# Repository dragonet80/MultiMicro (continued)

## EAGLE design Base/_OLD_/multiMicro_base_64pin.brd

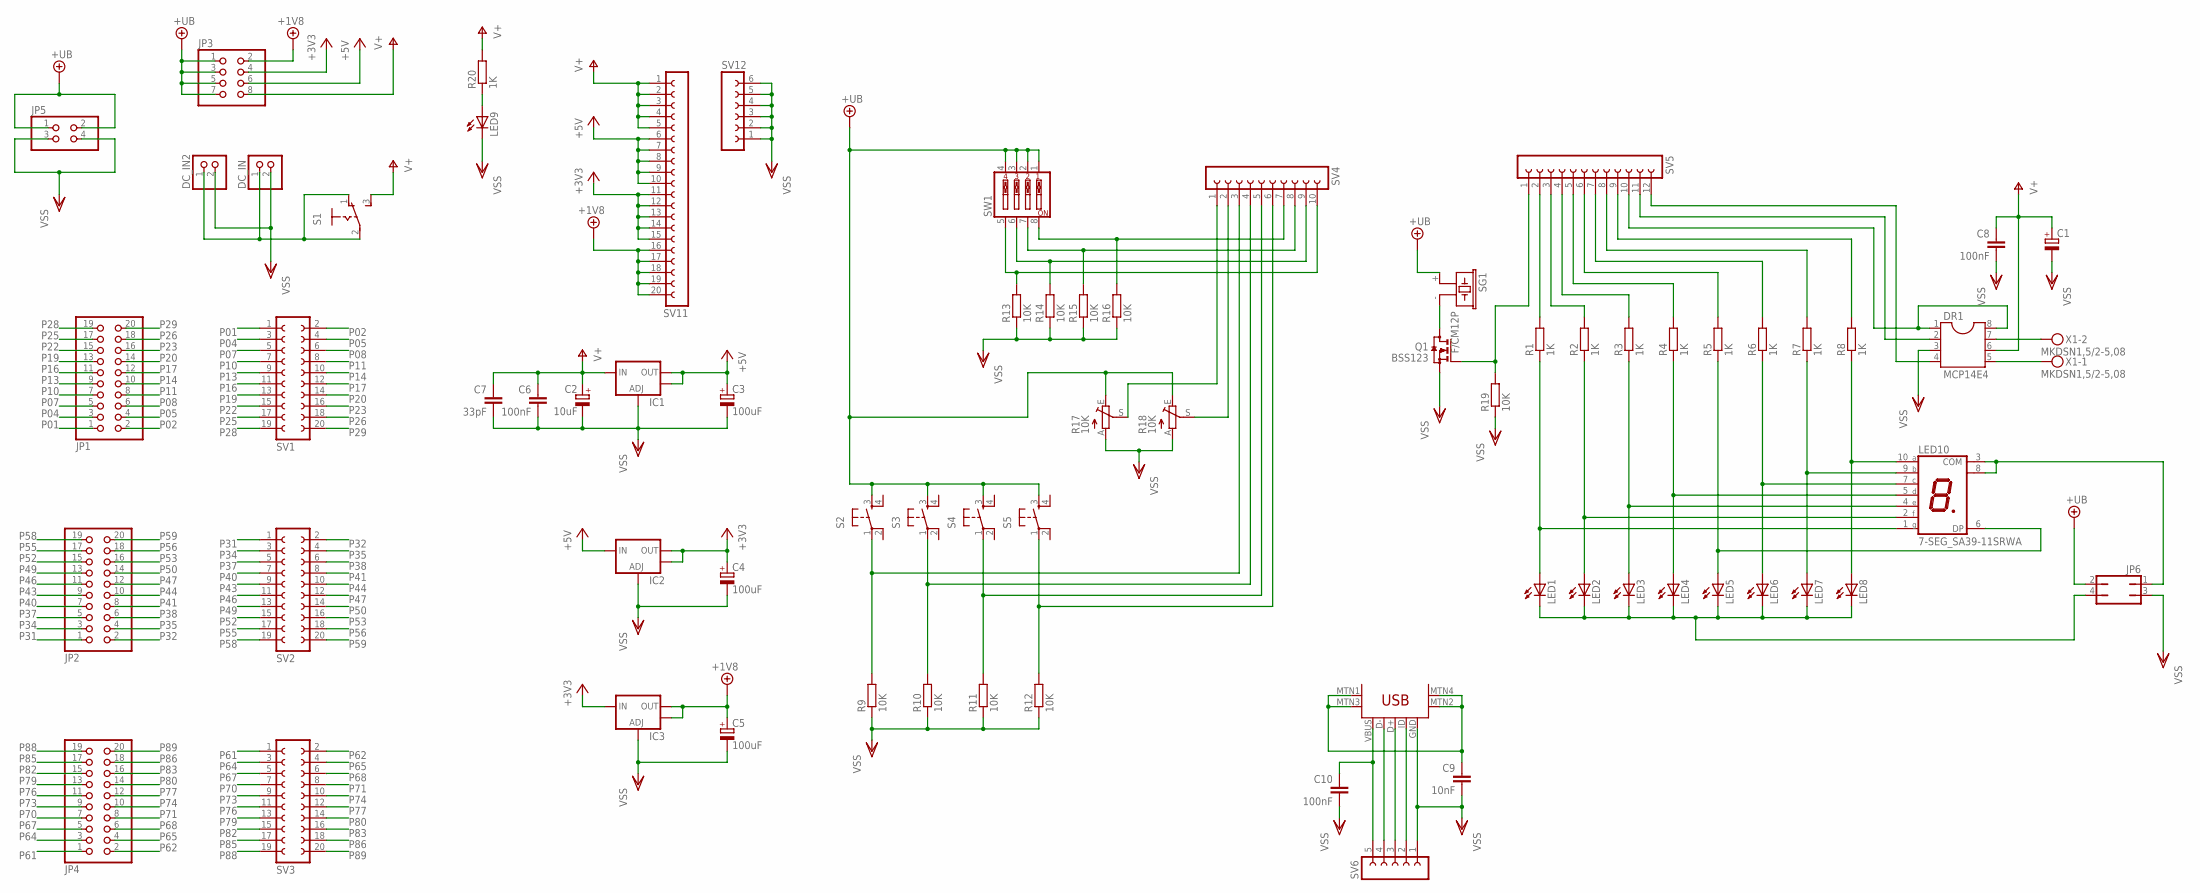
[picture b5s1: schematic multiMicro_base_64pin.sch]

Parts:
C1: CPOL-EU140CLH-0810; 140CLH-0810
C2: 10uF; SMC_C
C3, C4, C5: 100uF; CT7343
C6, C8, C10: 100nF; C0805
C7: 33pF; C0805
C9: 10nF; C0805
DC_IN, DC_IN2: PINHD-1X2/90; 1X02/90
DR1: MCP14E4; SOIC08
IC1, IC2, IC3: V_REG_LM1117SOT223; SOT223
JP1, JP2, JP4: PINHD-2X10/90; 2X10/90
JP3: PINHD-2X4; 2X04
JP5: PINHD-2X2/90; 2X02/90
JP6: JP2Q
LED1, LED2, LED3, LED4, LED5, LED6, LED7, LED8, LED9: LEDCHIP-LED0805; CHIP-LED0805
LED10: 7-SEG_SA39-11SRWA; SA39-11SRWA
Q1: BSS123; SOT23
R1, R2, R3, R4, R5, R6, R7, R8, R20: 1K; R0805
R9, R10, R11, R12, R13, R14, R15, R16, R19: 10K; R0805
R17, R18: 10K; CA6V
S1: 255SB
S2, S3, S4, S5: TAC_SWITCHPTH; TACTILE-PTH
SG1: F/CM12P
SV1, SV2, SV3: FE10-2
SV4: FE10-1; FE10
SV5: FE12-1; FE12
SV6: FE05-1
SV11: FE20-1; FE20
SV12: FE06-1; FE06
SW1: SW_DIP-4; EDG-04
U$1: USB-MINIB-5PIN; USB-MINIB
X1: MKDSN1,5/2-5,08

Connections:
+3V3: C4.+, IC2.2 (OUT), IC2.4 (OUT), IC3.3 (IN), JP3.4, SV11.11, SV11.12, SV11.13, SV11.14, SV11.15
+5V: C3.+, IC1.2 (OUT), IC1.4 (OUT), IC2.3 (IN), JP3.6, SV11.6, SV11.7, SV11.8, SV11.9, SV11.10
+18V: C5.+, IC3.2 (OUT), IC3.4 (OUT), JP3.2, SV11.16, SV11.17, SV11.18, SV11.19, SV11.20
+UB: JP3.1, JP3.3, JP3.5, JP3.7, JP5.1, JP5.2, JP6.2, R17.E, R18.E, S2.3, S3.3, S4.3, S5.3, SG1.+ (1), SW1.1, SW1.2, SW1.3, SW1.4
unnamed: LED1.A, LED10.1 (G), R1.1
unnamed: LED2.A, LED10.2 (F), R2.1
unnamed: LED3.A, LED10.4 (E), R3.1
unnamed: LED4.A, LED10.5 (D), R4.1
unnamed: R2.2, SV5.3
unnamed: R3.2, SV5.4
unnamed: R1.2, SV5.2
unnamed: R4.2, SV5.5
unnamed: LED9.A, R20.1
unnamed: R18.S, SV4.2
unnamed: DR1.5, X1.1
unnamed: DR1.7, X1.2
unnamed: DR1.2, SV5.11
unnamed: DR1.4, SV5.12
unnamed: DR1.1, DR1.8, SV5.10
unnamed: JP6.4, LED1.C, LED2.C, LED3.C, LED4.C, LED5.C, LED6.C, LED7.C, LED8.C
unnamed: JP6.1, LED10.3 (COM), LED10.8 (COM)
unnamed: Q1.3 (D), SG1.- (2)
unnamed: SV6.2, U$1.ID
unnamed: LED5.A, LED10.6 (DP), R5.1
unnamed: C9.1, U$1.MTN1 (MTN2), U$1.MTN2 (MTN3), U$1.MTN3 (MTN1), U$1.MTN4
unnamed: SV6.3, U$1.D+
unnamed: SV6.4, U$1.D-
unnamed: C10.1, SV6.5, U$1.VBUS
unnamed: DC_IN.1, DC_IN2.1, S1.1 (O), S1.2
unnamed: LED6.A, LED10.7 (C), R6.1
unnamed: LED7.A, LED10.9 (B), R7.1
unnamed: LED8.A, LED10.10 (A), R8.1
unnamed: R9.2, S2.1, SV4.3
unnamed: R10.2, S3.1, SV4.4
unnamed: R11.2, S4.1, SV4.5
unnamed: R12.2, S5.1, SV4.6
unnamed: Q1.1 (G), R19.2, SV5.1
unnamed: R17.S, SV4.1
unnamed: R6.2, SV5.7
unnamed: R7.2, SV5.8
unnamed: R5.2, SV5.6
unnamed: R8.2, SV5.9
unnamed: R13.2, SV4.10, SW1.5
unnamed: R14.2, SV4.9, SW1.6
unnamed: R15.2, SV4.8, SW1.7
unnamed: R16.2, SV4.7, SW1.8
P01: JP1.1, SV1.1
P02: JP1.2, SV1.2
P04: JP1.3, SV1.3
P05: JP1.4, SV1.4
P07: JP1.5, SV1.5
P08: JP1.6, SV1.6
P10: JP1.7, SV1.7
P11: JP1.8, SV1.8
P13: JP1.9, SV1.9
P14: JP1.10, SV1.10
P16: JP1.11, SV1.11
P17: JP1.12, SV1.12
P19: JP1.13, SV1.13
P20: JP1.14, SV1.14
P22: JP1.15, SV1.15
P23: JP1.16, SV1.16
P25: JP1.17, SV1.17
P26: JP1.18, SV1.18
P28: JP1.19, SV1.19
P29: JP1.20, SV1.20
P31: JP2.1, SV2.1
P32: JP2.2, SV2.2
P34: JP2.3, SV2.3
P35: JP2.4, SV2.4
P37: JP2.5, SV2.5
P38: JP2.6, SV2.6
P40: JP2.7, SV2.7
P41: JP2.8, SV2.8
P43: JP2.9, SV2.9
P44: JP2.10, SV2.10
P46: JP2.11, SV2.11
P47: JP2.12, SV2.12
P49: JP2.13, SV2.13
P50: JP2.14, SV2.14
P52: JP2.15, SV2.15
P53: JP2.16, SV2.16
P55: JP2.17, SV2.17
P56: JP2.18, SV2.18
P58: JP2.19, SV2.19
P59: JP2.20, SV2.20
P61: JP4.1, SV3.1
P62: JP4.2, SV3.2
P64: JP4.3, SV3.3
P65: JP4.4, SV3.4
P67: JP4.5, SV3.5
P68: JP4.6, SV3.6
P70: JP4.7, SV3.7
P71: JP4.8, SV3.8
P73: JP4.9, SV3.9
P74: JP4.10, SV3.10
P76: JP4.11, SV3.11
P77: JP4.12, SV3.12
P79: JP4.13, SV3.13
P80: JP4.14, SV3.14
P82: JP4.15, SV3.15
P83: JP4.16, SV3.16
P85: JP4.17, SV3.17
P86: JP4.18, SV3.18
P88: JP4.19, SV3.19
P89: JP4.20, SV3.20
V+: C1.+, C2.+, C6.1, C7.1, C8.1, DR1.6, IC1.3 (IN), JP3.8, R20.2, S1.3 (S), SV11.1, SV11.2, SV11.3, SV11.4, SV11.5
VSS: C1.-, C2.-, C3.-, C4.-, C5.-, C6.2, C7.2, C8.2, C9.2, C10.2, DC_IN.2, DC_IN2.2, DR1.3, IC1.1 (ADJ), IC2.1 (ADJ), IC3.1 (ADJ), JP5.3, JP5.4, JP6.3, LED9.C, Q1.2 (S), R9.1, R10.1, R11.1, R12.1, R13.1, R14.1, R15.1, R16.1, R17.A, R18.A, R19.1, SV6.1, SV12.1, SV12.2, SV12.3, SV12.4, SV12.5, SV12.6, U$1.GND

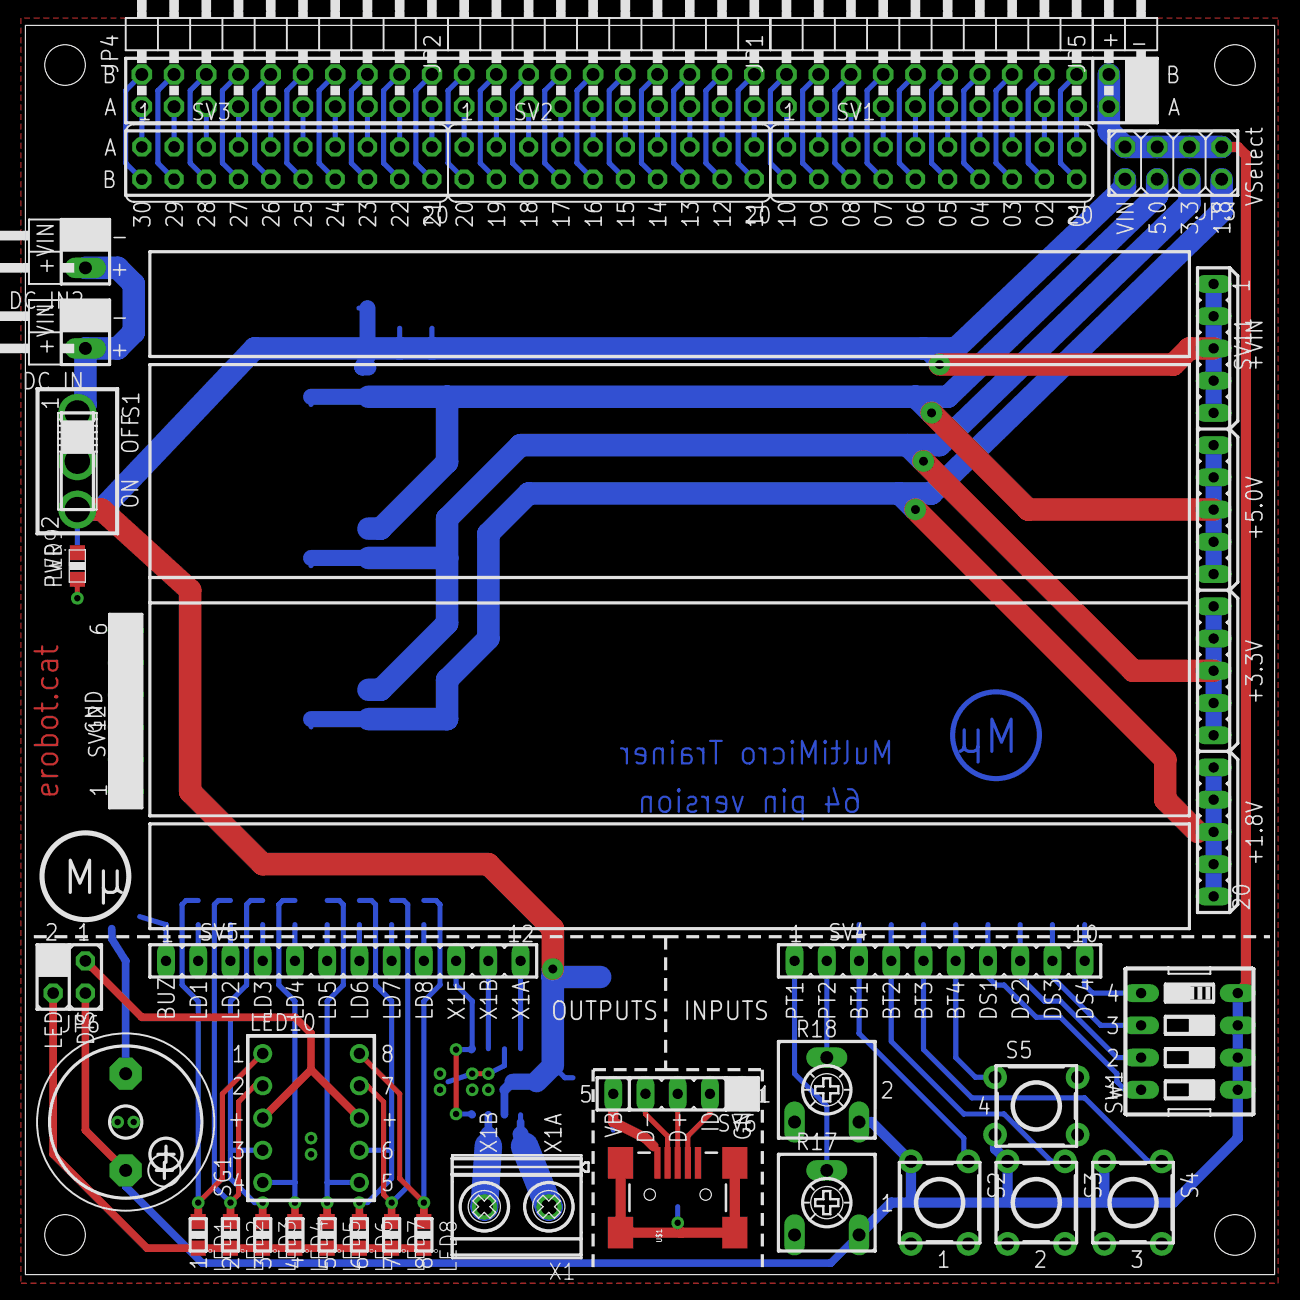
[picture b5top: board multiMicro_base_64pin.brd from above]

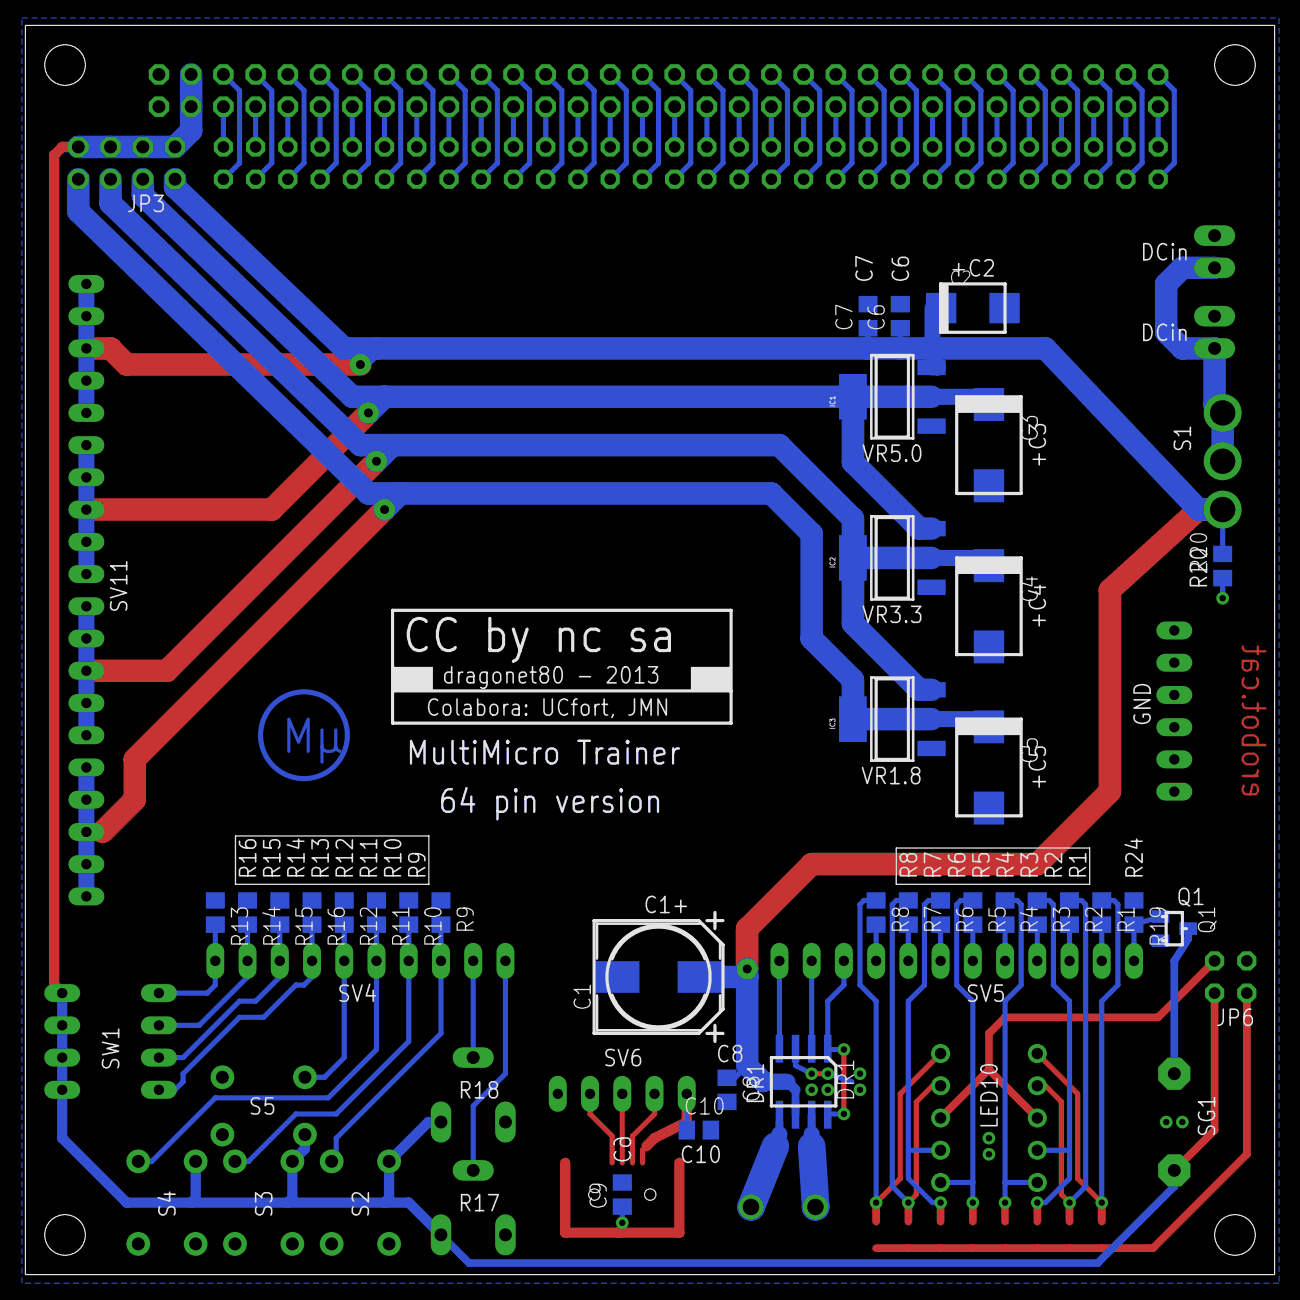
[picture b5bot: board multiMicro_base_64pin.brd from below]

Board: 2 copper layers, 98.4 x 98.4 mm, 70 parts (33 on the bottom side), 108 nets.

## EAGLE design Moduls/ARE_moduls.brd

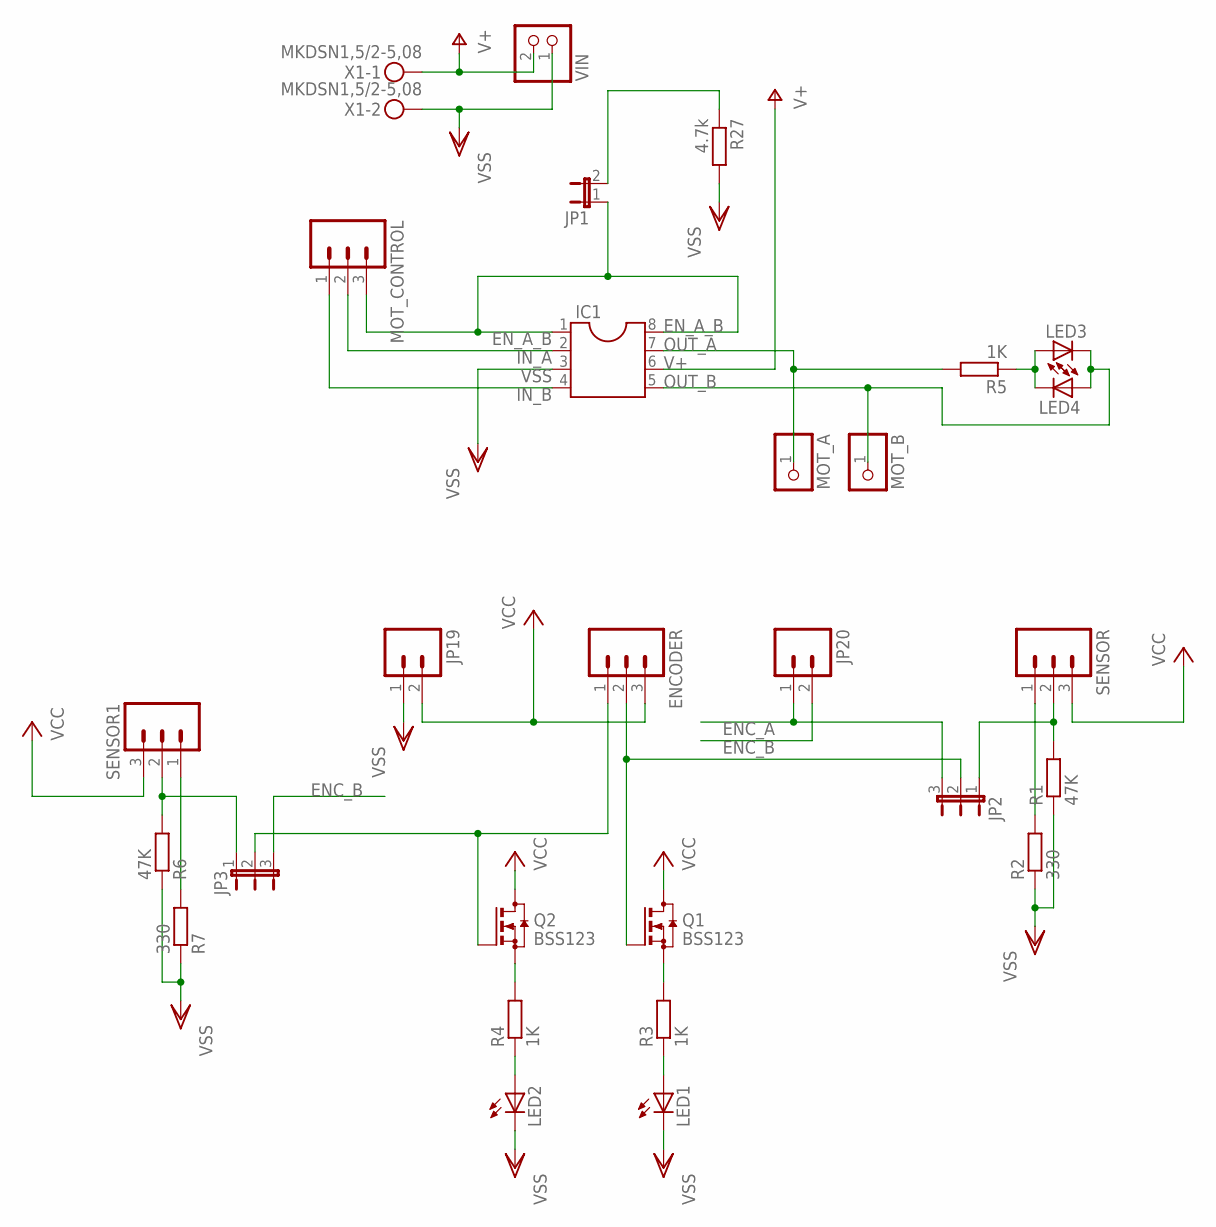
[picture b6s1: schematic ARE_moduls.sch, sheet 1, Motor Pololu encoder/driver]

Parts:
ENCODER: M03PTH; 1X03
IC1: DIL8S; SOCKET-08
JP1: JP1E; JP1
JP2, JP3: JP2E; JP2
JP19, JP20: M02PTH; 1X02
LED1, LED2, LED3, LED4: LEDCHIPLED_0805; CHIPLED_0805
MOT_A: PINHD-1X1; 1X01
MOT_B: PINHD-1X1; 1X01
MOT_CONTROL: M03PTH; 1X03
Q1, Q2: BSS123; SOT23
R1, R6: 47K; M0805
R2, R7: 330; M0805
R3, R4, R5: 1K; M0805
R27: 4.7k; R0805
SENSOR, SENSOR1: M03PTH; 1X03
VIN: PINHD-1X2; 1X02
X1: MKDSN1,5/2-5,08

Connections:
ENC_A: JP2.3, JP20.1
ENC_B: JP3.3, JP20.2
EN_A_B: IC1.1, IC1.8, JP1.1, MOT_CONTROL.3
IN_A: IC1.2, MOT_CONTROL.2
IN_B: IC1.4, MOT_CONTROL.1
unnamed: JP1.2, R27.1
unnamed: R2.2, SENSOR.1
unnamed: ENCODER.2, JP2.2, Q1.1 (G)
unnamed: JP2.1, R1.2, SENSOR.2
unnamed: Q1.2 (S), R3.2
unnamed: LED1.A, R3.1
unnamed: Q2.2 (S), R4.2
unnamed: LED2.A, R4.1
unnamed: LED3.A, LED4.C, R5.1
unnamed: R7.2, SENSOR1.1
unnamed: JP3.1, R6.2, SENSOR1.2
unnamed: ENCODER.1, JP3.2, Q2.1 (G)
OUT_A: IC1.7, MOT_A.1, R5.2
OUT_B: IC1.5, LED3.C, LED4.A, MOT_B.1
V+: IC1.6, VIN.2, X1.1
VCC: ENCODER.3, JP19.2, Q1.3 (D), Q2.3 (D), SENSOR.3, SENSOR1.3; also elsewhere on the board
VSS: IC1.3, JP19.1, LED1.C, LED2.C, R1.1, R2.1, R6.1, R7.1, R27.2, VIN.1, X1.2; also elsewhere on the board

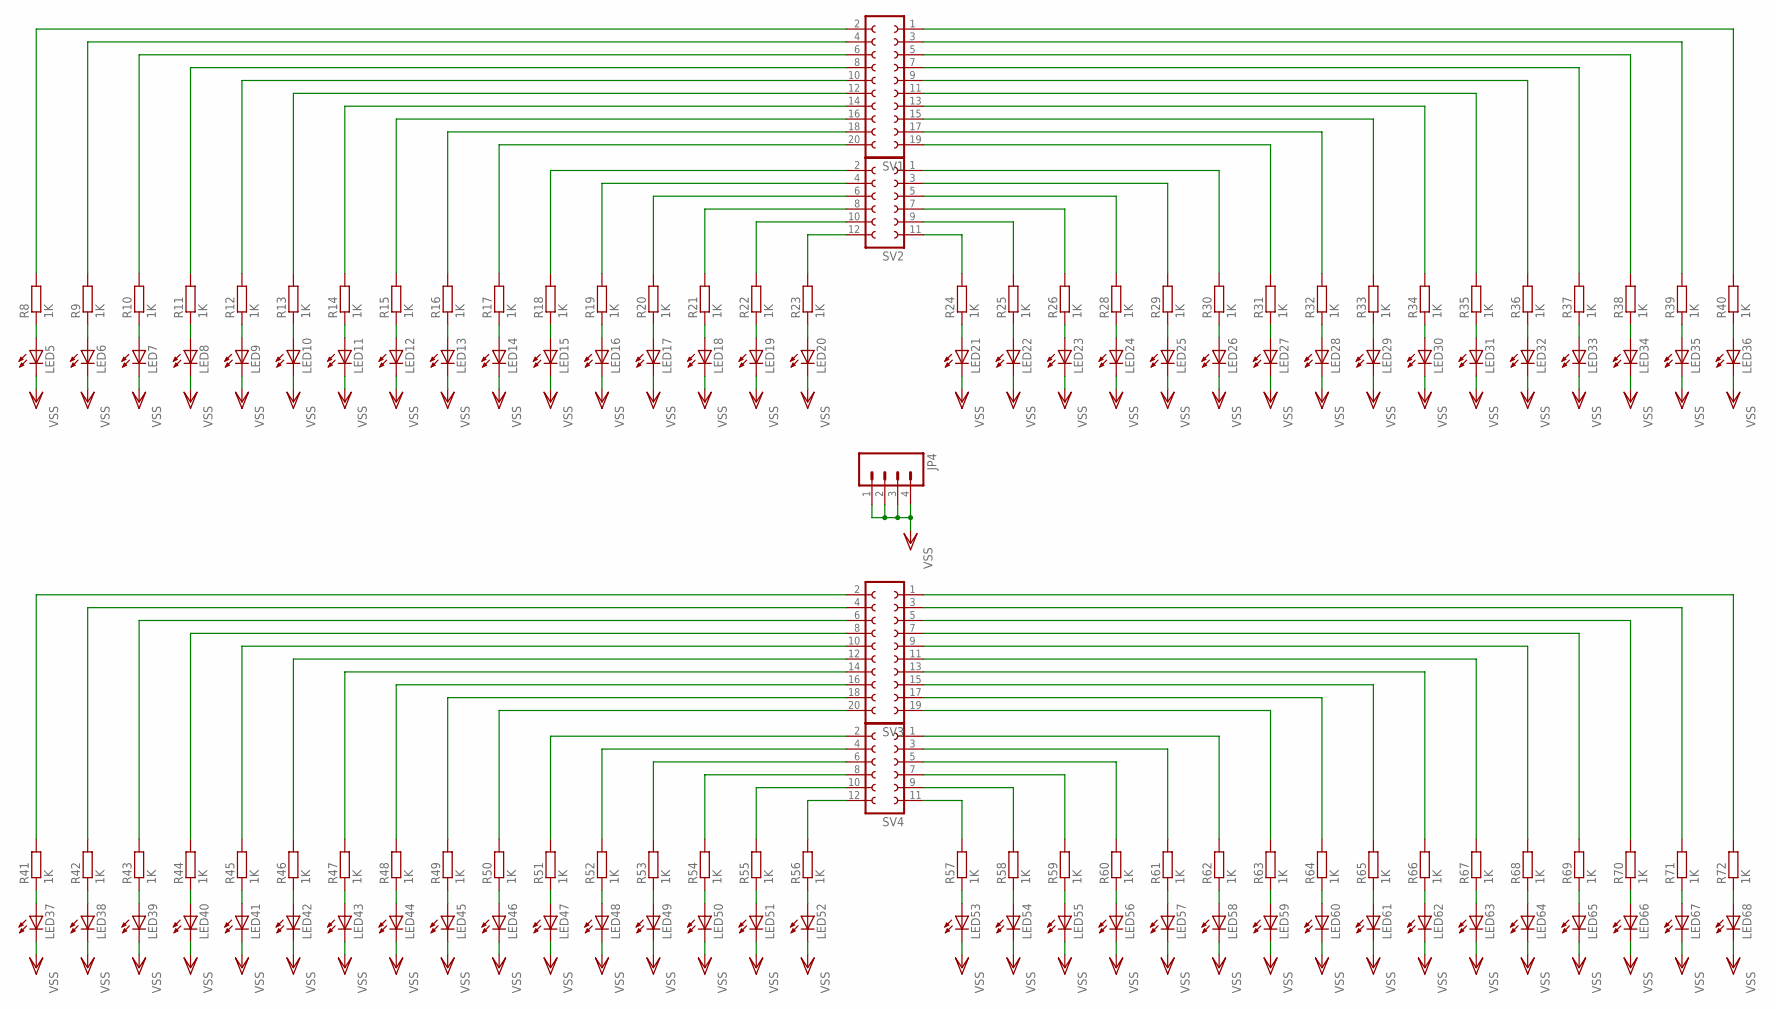
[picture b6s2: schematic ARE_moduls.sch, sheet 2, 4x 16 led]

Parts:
JP4: M04PTH; 1X04
LED5, LED6, LED7, LED8, LED9, LED10, LED11, LED12, LED13, LED14, LED15, LED16, LED17, LED18, LED19, LED20, LED21, LED22, LED23, LED24, LED25, LED26, LED27, LED28, LED29, LED30, LED31, LED32, LED33, LED34, LED35, LED36, LED37, LED38, LED39, LED40, LED41, LED42, LED43, LED44, LED45, LED46, LED47, LED48, LED49, LED50, LED51, LED52, LED53, LED54, LED55, LED56, LED57, LED58, LED59, LED60, LED61, LED62, LED63, LED64, LED65, LED66, LED67, LED68: LEDCHIPLED_0805; CHIPLED_0805
R8, R9, R10, R11, R12, R13, R14, R15, R16, R17, R18, R19, R20, R21, R22, R23, R24, R25, R26, R28, R29, R30, R31, R32, R33, R34, R35, R36, R37, R38, R39, R40, R41, R42, R43, R44, R45, R46, R47, R48, R49, R50, R51, R52, R53, R54, R55, R56, R57, R58, R59, R60, R61, R62, R63, R64, R65, R66, R67, R68, R69, R70, R71, R72: 1K; M0805
SV1, SV3: FE10-2
SV2, SV4: FE06-2

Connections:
unnamed: LED5.A, R8.1
unnamed: LED6.A, R9.1
unnamed: LED7.A, R10.1
unnamed: LED8.A, R11.1
unnamed: LED9.A, R12.1
unnamed: LED10.A, R13.1
unnamed: LED11.A, R14.1
unnamed: LED12.A, R15.1
unnamed: LED13.A, R16.1
unnamed: LED14.A, R17.1
unnamed: LED15.A, R18.1
unnamed: LED16.A, R19.1
unnamed: LED17.A, R20.1
unnamed: LED18.A, R21.1
unnamed: LED19.A, R22.1
unnamed: LED20.A, R23.1
unnamed: R23.2, SV2.12
unnamed: LED37.A, R41.1
unnamed: R22.2, SV2.10
unnamed: R21.2, SV2.8
unnamed: R20.2, SV2.6
unnamed: R19.2, SV2.4
unnamed: R18.2, SV2.2
unnamed: R17.2, SV1.20
unnamed: R16.2, SV1.18
unnamed: R15.2, SV1.16
unnamed: R14.2, SV1.14
unnamed: R13.2, SV1.12
unnamed: R12.2, SV1.10
unnamed: R11.2, SV1.8
unnamed: R10.2, SV1.6
unnamed: R9.2, SV1.4
unnamed: R8.2, SV1.2
unnamed: LED21.A, R24.1
unnamed: LED22.A, R25.1
unnamed: LED23.A, R26.1
unnamed: LED24.A, R28.1
unnamed: LED25.A, R29.1
unnamed: LED26.A, R30.1
unnamed: LED27.A, R31.1
unnamed: LED28.A, R32.1
unnamed: LED29.A, R33.1
unnamed: LED30.A, R34.1
unnamed: LED31.A, R35.1
unnamed: LED32.A, R36.1
unnamed: LED33.A, R37.1
unnamed: LED34.A, R38.1
unnamed: LED35.A, R39.1
unnamed: LED36.A, R40.1
unnamed: R24.2, SV2.11
unnamed: R25.2, SV2.9
unnamed: R26.2, SV2.7
unnamed: R28.2, SV2.5
unnamed: R29.2, SV2.3
unnamed: R30.2, SV2.1
unnamed: R31.2, SV1.19
unnamed: R32.2, SV1.17
unnamed: R33.2, SV1.15
unnamed: R34.2, SV1.13
unnamed: R35.2, SV1.11
unnamed: R36.2, SV1.9
unnamed: R37.2, SV1.7
unnamed: R38.2, SV1.5
unnamed: R39.2, SV1.3
unnamed: R40.2, SV1.1
unnamed: LED38.A, R42.1
unnamed: LED39.A, R43.1
unnamed: LED40.A, R44.1
unnamed: LED41.A, R45.1
unnamed: LED42.A, R46.1
unnamed: LED43.A, R47.1
unnamed: LED44.A, R48.1
unnamed: LED45.A, R49.1
unnamed: LED46.A, R50.1
unnamed: LED47.A, R51.1
unnamed: LED48.A, R52.1
unnamed: LED49.A, R53.1
unnamed: LED50.A, R54.1
unnamed: LED51.A, R55.1
unnamed: LED52.A, R56.1
unnamed: R56.2, SV4.12
unnamed: R55.2, SV4.10
unnamed: R54.2, SV4.8
unnamed: R53.2, SV4.6
unnamed: R52.2, SV4.4
unnamed: R51.2, SV4.2
unnamed: R50.2, SV3.20
unnamed: R49.2, SV3.18
unnamed: R48.2, SV3.16
unnamed: R47.2, SV3.14
unnamed: R46.2, SV3.12
unnamed: R45.2, SV3.10
unnamed: R44.2, SV3.8
unnamed: R43.2, SV3.6
unnamed: R42.2, SV3.4
unnamed: R41.2, SV3.2
unnamed: LED53.A, R57.1
unnamed: LED54.A, R58.1
unnamed: LED55.A, R59.1
unnamed: LED56.A, R60.1
unnamed: LED57.A, R61.1
unnamed: LED58.A, R62.1
unnamed: LED59.A, R63.1
unnamed: LED60.A, R64.1
unnamed: LED61.A, R65.1
unnamed: LED62.A, R66.1
unnamed: LED63.A, R67.1
unnamed: LED64.A, R68.1
unnamed: LED65.A, R69.1
unnamed: LED66.A, R70.1
unnamed: LED67.A, R71.1
unnamed: LED68.A, R72.1
unnamed: R57.2, SV4.11
unnamed: R58.2, SV4.9
unnamed: R59.2, SV4.7
unnamed: R60.2, SV4.5
unnamed: R61.2, SV4.3
unnamed: R62.2, SV4.1
unnamed: R63.2, SV3.19
unnamed: R64.2, SV3.17
unnamed: R65.2, SV3.15
unnamed: R66.2, SV3.13
unnamed: R67.2, SV3.11
unnamed: R68.2, SV3.9
unnamed: R69.2, SV3.7
unnamed: R70.2, SV3.5
unnamed: R71.2, SV3.3
unnamed: R72.2, SV3.1
VSS: JP4.1, JP4.2, JP4.3, JP4.4, LED5.C, LED6.C, LED7.C, LED8.C, LED9.C, LED10.C, LED11.C, LED12.C, LED13.C, LED14.C, LED15.C, LED16.C, LED17.C, LED18.C, LED19.C, LED20.C, LED21.C, LED22.C, LED23.C, LED24.C, LED25.C, LED26.C, LED27.C, LED28.C, LED29.C, LED30.C, LED31.C, LED32.C, LED33.C, LED34.C, LED35.C, LED36.C, LED37.C, LED38.C, LED39.C, LED40.C, LED41.C, LED42.C, LED43.C, LED44.C, LED45.C, LED46.C, LED47.C, LED48.C, LED49.C, LED50.C, LED51.C, LED52.C, LED53.C, LED54.C, LED55.C, LED56.C, LED57.C, LED58.C, LED59.C, LED60.C, LED61.C, LED62.C, LED63.C, LED64.C, LED65.C, LED66.C, LED67.C, LED68.C; also elsewhere on the board

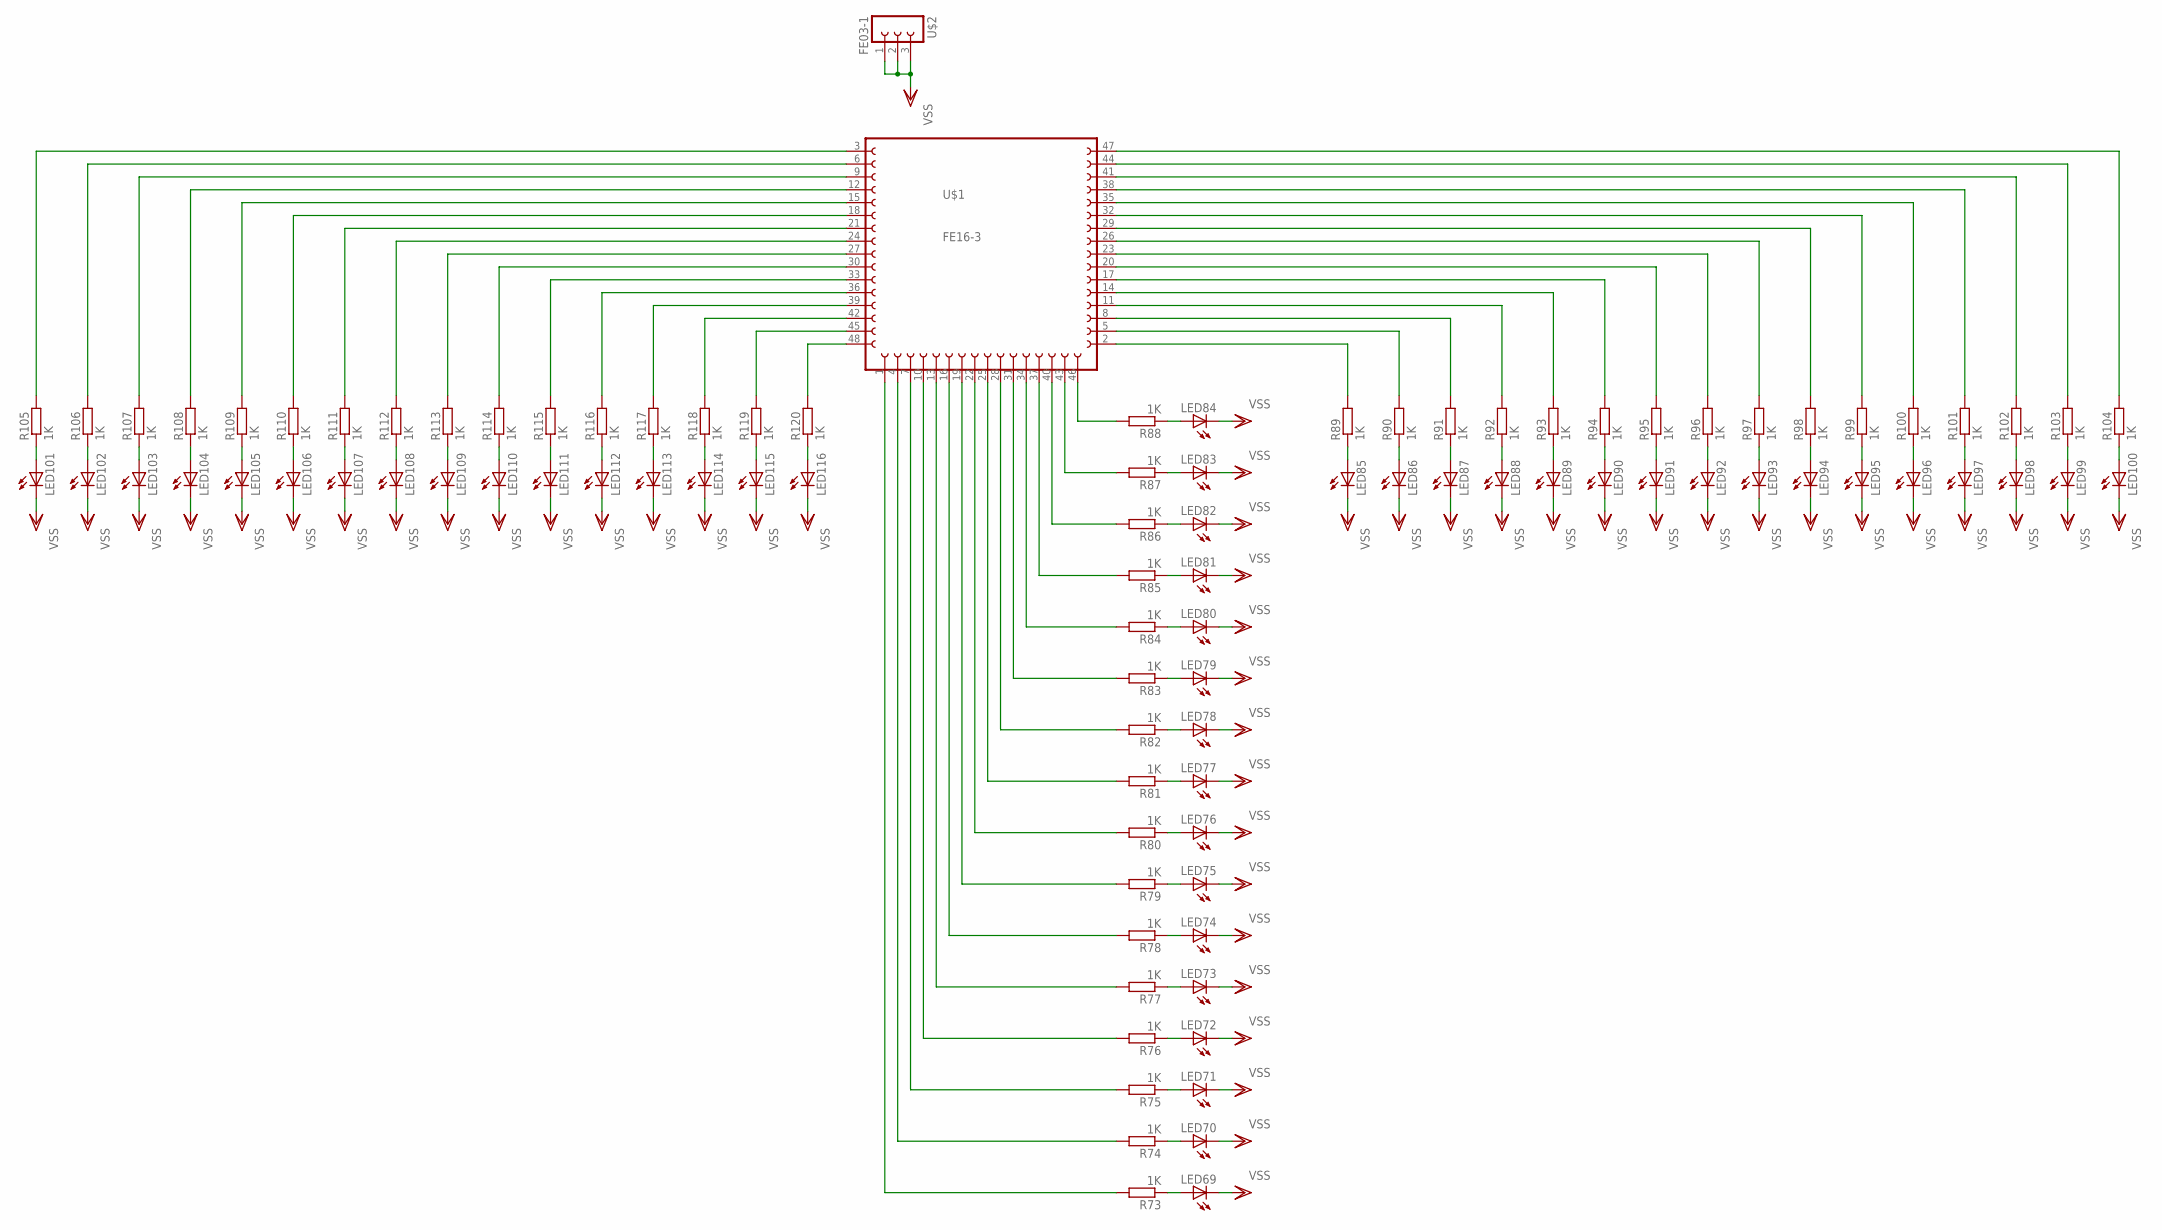
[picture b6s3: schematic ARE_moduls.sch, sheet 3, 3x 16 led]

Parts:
LED69, LED70, LED71, LED72, LED73, LED74, LED75, LED76, LED77, LED78, LED79, LED80, LED81, LED82, LED83, LED84, LED85, LED86, LED87, LED88, LED89, LED90, LED91, LED92, LED93, LED94, LED95, LED96, LED97, LED98, LED99, LED100, LED101, LED102, LED103, LED104, LED105, LED106, LED107, LED108, LED109, LED110, LED111, LED112, LED113, LED114, LED115, LED116: LEDCHIPLED_0805; CHIPLED_0805
R73, R74, R75, R76, R77, R78, R79, R80, R81, R82, R83, R84, R85, R86, R87, R88, R89, R90, R91, R92, R93, R94, R95, R96, R97, R98, R99, R100, R101, R102, R103, R104, R105, R106, R107, R108, R109, R110, R111, R112, R113, R114, R115, R116, R117, R118, R119, R120: 1K; M0805
U$1: FE16-3
U$2: FE03-1

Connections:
unnamed: LED69.A, R73.1
unnamed: LED70.A, R74.1
unnamed: LED71.A, R75.1
unnamed: LED72.A, R76.1
unnamed: LED73.A, R77.1
unnamed: LED74.A, R78.1
unnamed: LED75.A, R79.1
unnamed: LED76.A, R80.1
unnamed: LED77.A, R81.1
unnamed: LED78.A, R82.1
unnamed: LED79.A, R83.1
unnamed: LED80.A, R84.1
unnamed: LED81.A, R85.1
unnamed: LED82.A, R86.1
unnamed: LED83.A, R87.1
unnamed: LED84.A, R88.1
unnamed: R88.2, U$1.46
unnamed: R87.2, U$1.43
unnamed: R86.2, U$1.40
unnamed: R85.2, U$1.37
unnamed: R84.2, U$1.34
unnamed: R83.2, U$1.31
unnamed: R82.2, U$1.28
unnamed: R81.2, U$1.25
unnamed: R80.2, U$1.22
unnamed: R79.2, U$1.19
unnamed: R78.2, U$1.16
unnamed: R77.2, U$1.13
unnamed: R76.2, U$1.10
unnamed: R75.2, U$1.7
unnamed: R74.2, U$1.4
unnamed: R73.2, U$1.1
unnamed: LED85.A, R89.1
unnamed: LED86.A, R90.1
unnamed: LED87.A, R91.1
unnamed: LED88.A, R92.1
unnamed: LED89.A, R93.1
unnamed: LED90.A, R94.1
unnamed: LED91.A, R95.1
unnamed: LED92.A, R96.1
unnamed: LED93.A, R97.1
unnamed: LED94.A, R98.1
unnamed: LED95.A, R99.1
unnamed: LED96.A, R100.1
unnamed: LED97.A, R101.1
unnamed: LED98.A, R102.1
unnamed: LED99.A, R103.1
unnamed: LED100.A, R104.1
unnamed: R89.2, U$1.2
unnamed: R90.2, U$1.5
unnamed: R91.2, U$1.8
unnamed: R92.2, U$1.11
unnamed: R93.2, U$1.14
unnamed: R94.2, U$1.17
unnamed: R95.2, U$1.20
unnamed: R96.2, U$1.23
unnamed: R97.2, U$1.26
unnamed: R98.2, U$1.29
unnamed: R99.2, U$1.32
unnamed: R100.2, U$1.35
unnamed: R101.2, U$1.38
unnamed: R102.2, U$1.41
unnamed: R103.2, U$1.44
unnamed: R104.2, U$1.47
unnamed: LED101.A, R105.1
unnamed: LED102.A, R106.1
unnamed: LED103.A, R107.1
unnamed: LED104.A, R108.1
unnamed: LED105.A, R109.1
unnamed: LED106.A, R110.1
unnamed: LED107.A, R111.1
unnamed: LED108.A, R112.1
unnamed: LED109.A, R113.1
unnamed: LED110.A, R114.1
unnamed: LED111.A, R115.1
unnamed: LED112.A, R116.1
unnamed: LED113.A, R117.1
unnamed: LED114.A, R118.1
unnamed: LED115.A, R119.1
unnamed: LED116.A, R120.1
unnamed: R120.2, U$1.48
unnamed: R119.2, U$1.45
unnamed: R118.2, U$1.42
unnamed: R117.2, U$1.39
unnamed: R116.2, U$1.36
unnamed: R115.2, U$1.33
unnamed: R114.2, U$1.30
unnamed: R113.2, U$1.27
unnamed: R112.2, U$1.24
unnamed: R111.2, U$1.21
unnamed: R110.2, U$1.18
unnamed: R109.2, U$1.15
unnamed: R108.2, U$1.12
unnamed: R107.2, U$1.9
unnamed: R106.2, U$1.6
unnamed: R105.2, U$1.3
VSS: LED69.C, LED70.C, LED71.C, LED72.C, LED73.C, LED74.C, LED75.C, LED76.C, LED77.C, LED78.C, LED79.C, LED80.C, LED81.C, LED82.C, LED83.C, LED84.C, LED85.C, LED86.C, LED87.C, LED88.C, LED89.C, LED90.C, LED91.C, LED92.C, LED93.C, LED94.C, LED95.C, LED96.C, LED97.C, LED98.C, LED99.C, LED100.C, LED101.C, LED102.C, LED103.C, LED104.C, LED105.C, LED106.C, LED107.C, LED108.C, LED109.C, LED110.C, LED111.C, LED112.C, LED113.C, LED114.C, LED115.C, LED116.C, U$2.1, U$2.2, U$2.3; also elsewhere on the board
